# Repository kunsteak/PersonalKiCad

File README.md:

# KunsteakKicad

A collection of footprints, symbols, and 3D models for building mechanical keyboards with Kicad.

# Common grid sizes

-   18x17mm (Choc)
    -   1.00u - X: 18, Y:17
    -   0.50u - X: 9, Y: 8.5
    -   0.25u - X: 4.5, Y: 4.25
-   19.05x19.05 (MX/Alps)
    -   1.00u - X: 19.05, Y: 19.05
    -   0.50u - X: 9.525, Y: 9.525
    -   0.25u X: 4.7625, Y: 4.7625

# Common Shortcuts

-   **Add (A)** - Add a footprint or symbol.
-   **Set Origin Point (S)** - Set where everything else will move in relation to.
-   **Move with Reference (])** - Move a footprint with a reference point.
-   **Track Tool (X)** - Place traces
-   **Add Via (V)** - Place a via to run a trace between PCB layers.
-   **Flip (F)** - Switch footprint between back and front of the PCB.

# Resources

Please refer to each library in order to understand the license it uses, most are Creative Commons CC-BY-SA 4.0.

-   [Keyswitch Library](https://github.com/kiswitch/kiswitch/tree/main) - 3D models and footprints for switches, stabilizers, and sockets.
-   [Raspberry Pi Pico](https://github.com/ncarandini/KiCad-RP-Pico) - 3D model, footprint, and symbol.
-   [Arduino Pro Micro](https://github.com/g200kg/kicad-lib-arduino) - Footprint and symbol.
-   [Marbastlib](https://github.com/ebastler/marbastlib) - Symbols.
-   [Kleeb](https://github.com/crides/kleeb) - 3D models, symbols, and footprints.
-   [Keebio](https://github.com/keebio/Keebio-Parts.pretty) - 3D models, footprints, and symbols.

# Credits

This collection of files was originally done by Joe Scotto of ScottoKeebs.

-   nice!nano - Base dimensions and placement by @Knotherface, can be found on GitHub as [Leopere](https://github.com/Leopere).

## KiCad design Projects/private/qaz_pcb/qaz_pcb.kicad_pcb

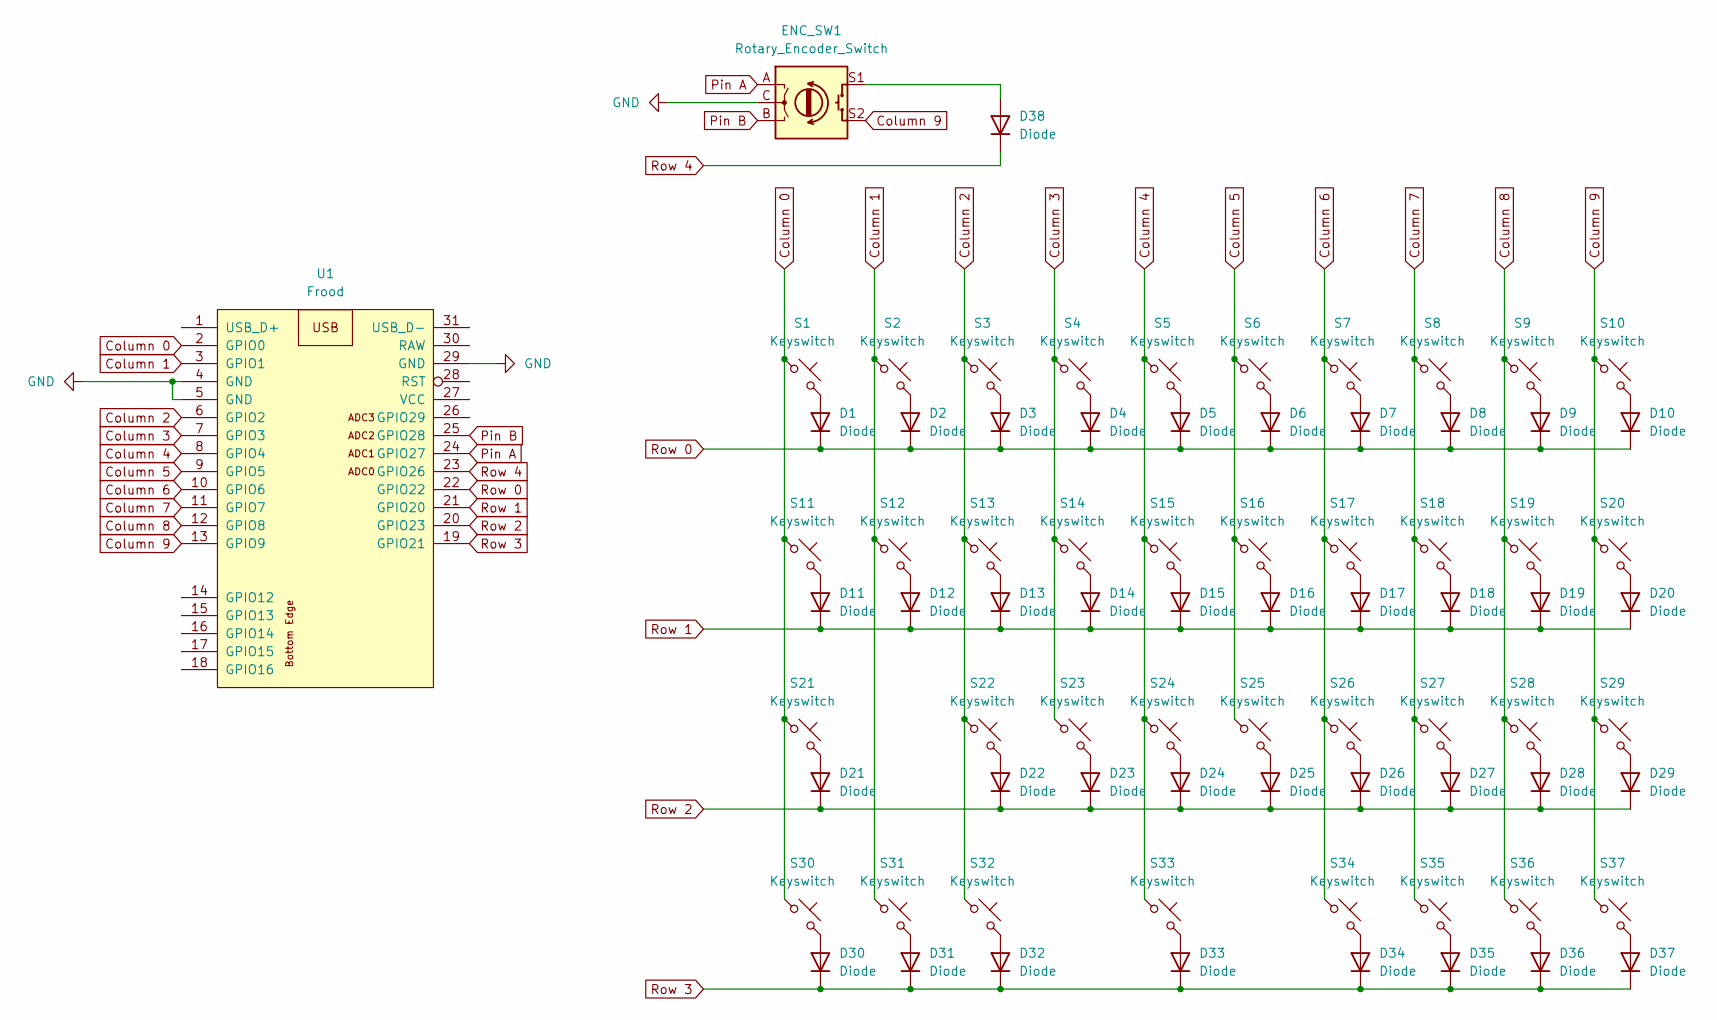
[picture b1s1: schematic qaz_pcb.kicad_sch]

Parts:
D1, D2, D3, D4, D5, D6, D7, D8, D9, D10, D11, D12, D13, D14, D15, D16, D17, D18, D19, D20, D21, D22, D23, D24, D25, D26, D27, D28, D29, D30, D31, D32, D33, D34, D35, D36, D37, D38: Diode; Diode_SOD-123
ENC_SW1: Rotary_Encoder_Switch; Rotary_Encoder_PEC11R-4220K-S0024
S1, S2, S3, S4, S5, S6, S7, S8, S9, S12, S13, S14, S15, S16, S17, S18, S19, S20, S22, S23, S24, S25, S26, S27, S28, S29, S30, S31, S32, S35, S36, S37: Keyswitch; Hotswap_MX_1.00u
S10, S11: Keyswitch; Hotswap_MX_1.25u
S21: Keyswitch; Hotswap_MX_1.75u
S33: Keyswitch; Hotswap_MX_2.25u
S34: Keyswitch; Hotswap_MX_2.00u
U1: Frood; Frood_PinHeader_2x13+5_P2.54mm_Labels_Top

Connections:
Column 0: S1.1, S11.1, S21.1, S30.1, U1.2 (GPIO0)
Column 1: S2.1, S12.1, S31.1, U1.3 (GPIO1)
Column 2: S3.1, S13.1, S22.1, S32.1, U1.6 (GPIO2)
Column 3: S4.1, S14.1, S23.1, U1.7 (GPIO3)
Column 4: S5.1, S15.1, S24.1, S33.1, U1.8 (GPIO4)
Column 5: S6.1, S16.1, S25.1, U1.9 (GPIO5)
Column 6: S7.1, S17.1, S26.1, S34.1, U1.10 (GPIO6)
Column 7: S8.1, S18.1, S27.1, S35.1, U1.11 (GPIO7)
Column 8: S9.1, S19.1, S28.1, S36.1, U1.12 (GPIO8)
Column 9: ENC_SW1.S2, S10.1, S20.1, S29.1, S37.1, U1.13 (GPIO9)
GND: ENC_SW1.C, U1.4 (GND), U1.5 (GND), U1.29 (GND)
unnamed: D1.2 (A), S1.2
unnamed: D2.2 (A), S2.2
unnamed: D3.2 (A), S3.2
unnamed: D4.2 (A), S4.2
unnamed: D5.2 (A), S5.2
unnamed: D6.2 (A), S6.2
unnamed: D7.2 (A), S7.2
unnamed: D8.2 (A), S8.2
unnamed: D9.2 (A), S9.2
unnamed: D10.2 (A), S10.2
unnamed: D11.2 (A), S11.2
unnamed: D12.2 (A), S12.2
unnamed: D13.2 (A), S13.2
unnamed: D14.2 (A), S14.2
unnamed: D15.2 (A), S15.2
unnamed: D16.2 (A), S16.2
unnamed: D17.2 (A), S17.2
unnamed: D18.2 (A), S18.2
unnamed: D19.2 (A), S19.2
unnamed: D20.2 (A), S20.2
unnamed: D21.2 (A), S21.2
unnamed: D22.2 (A), S22.2
unnamed: D23.2 (A), S23.2
unnamed: D24.2 (A), S24.2
unnamed: D25.2 (A), S25.2
unnamed: D26.2 (A), S26.2
unnamed: D27.2 (A), S27.2
unnamed: D28.2 (A), S28.2
unnamed: D29.2 (A), S29.2
unnamed: D30.2 (A), S30.2
unnamed: D31.2 (A), S31.2
unnamed: D32.2 (A), S32.2
unnamed: D33.2 (A), S33.2
unnamed: D34.2 (A), S34.2
unnamed: D35.2 (A), S35.2
unnamed: D36.2 (A), S36.2
unnamed: D37.2 (A), S37.2
unnamed: D38.2 (A), ENC_SW1.S1
Pin A: ENC_SW1.A, U1.24 (GPIO27)
Pin B: ENC_SW1.B, U1.25 (GPIO28)
Row 0: D1.1 (K), D2.1 (K), D3.1 (K), D4.1 (K), D5.1 (K), D6.1 (K), D7.1 (K), D8.1 (K), D9.1 (K), D10.1 (K), U1.22 (GPIO22)
Row 1: D11.1 (K), D12.1 (K), D13.1 (K), D14.1 (K), D15.1 (K), D16.1 (K), D17.1 (K), D18.1 (K), D19.1 (K), D20.1 (K), U1.21 (GPIO20)
Row 2: D21.1 (K), D22.1 (K), D23.1 (K), D24.1 (K), D25.1 (K), D26.1 (K), D27.1 (K), D28.1 (K), D29.1 (K), U1.20 (GPIO23)
Row 3: D30.1 (K), D31.1 (K), D32.1 (K), D33.1 (K), D34.1 (K), D35.1 (K), D36.1 (K), D37.1 (K), U1.19 (GPIO21)
Row 4: D38.1 (K), U1.23 (GPIO26)

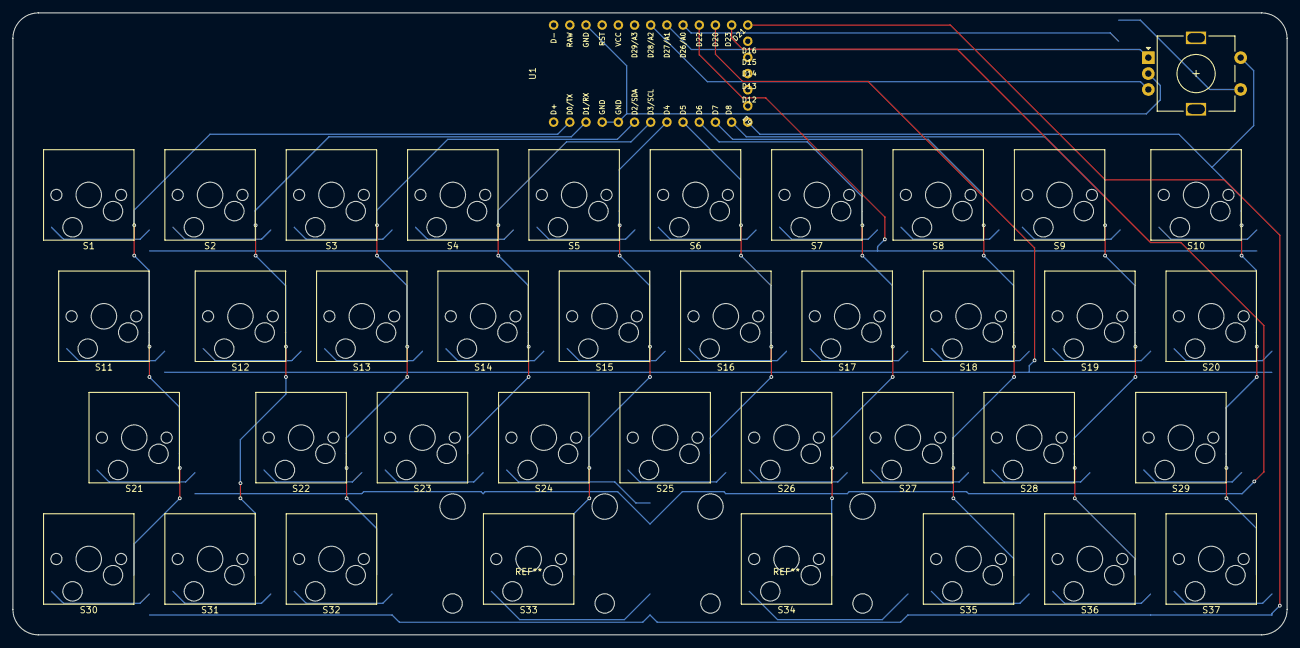
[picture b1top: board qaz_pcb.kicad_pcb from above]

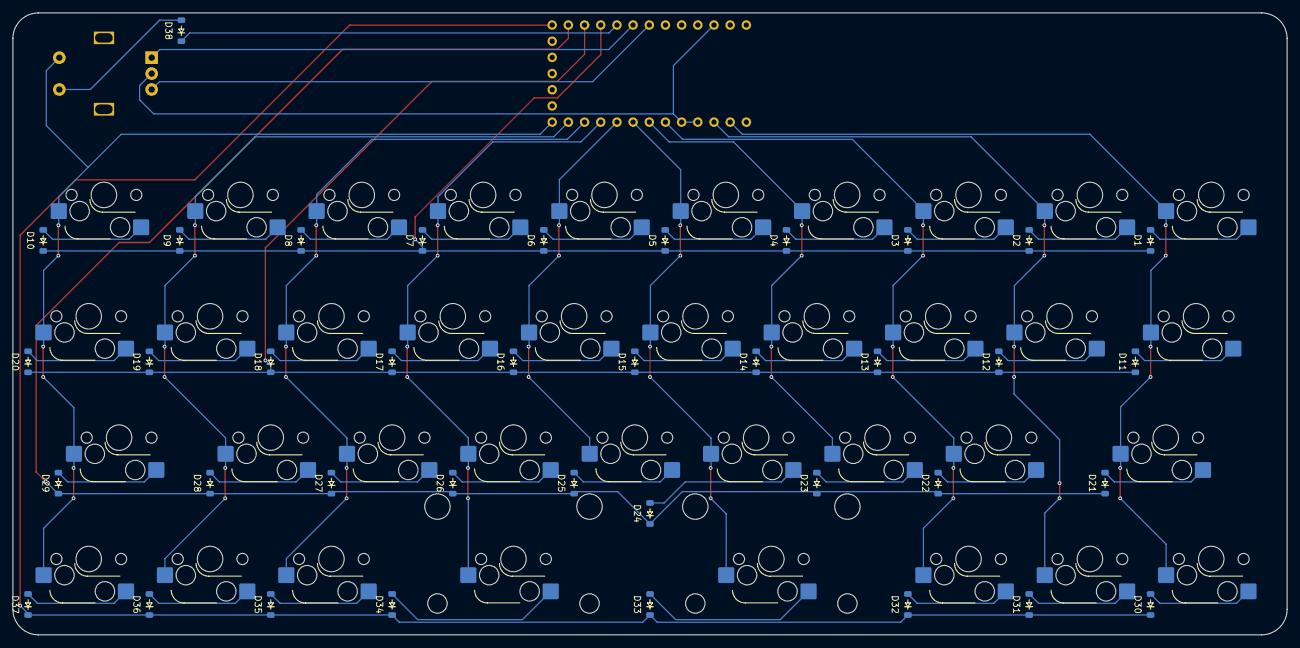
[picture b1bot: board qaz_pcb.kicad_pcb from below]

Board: 2 copper layers, 200.0 x 97.6 mm, 77 parts (38 on the bottom side), 56 nets.

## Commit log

2024-03-10 Initialised
2024-03-10 reverting to original naming scheme
2024-03-10 update
    - aligned everything
    - only connections need to be traced
2024-03-10 update
    - added proper frood 3d model (.step) alignment for the footprint
2024-03-10 update
    - removed folders and files created with newer versions of KiCAD
    - added frood-specific files
    - made all the necessary changes in both schematics and pcb editor (footprints)
2024-03-12 Finalised qaz pcb
    - finished the traces and connections
    - merged all necessary symbols, footprints, and 3d models into the ScottoKicad files and folders
    - added rotary encoder for the qaz (with schematic and 3d model)
2024-03-12 update
    - renamed everything from ScottoKeebs to Kunsteak
    - only updated the footprints and symbols relevant to the qaz project (all the other ones will have to be updated once they are used)
2024-03-12 update
    - fixed missing diode for rotary encoder
    TODO:
    - add mounting holes
    - create case
2024-03-13 Major update
    - renamed everything from 'scottokeebs' and 'kunsteak' to 'personal' for easier access and personalisation/individualisation.
    - updated README to include sources used in QAZ project
2024-03-14 update
    - added readme and pictures for qaz
